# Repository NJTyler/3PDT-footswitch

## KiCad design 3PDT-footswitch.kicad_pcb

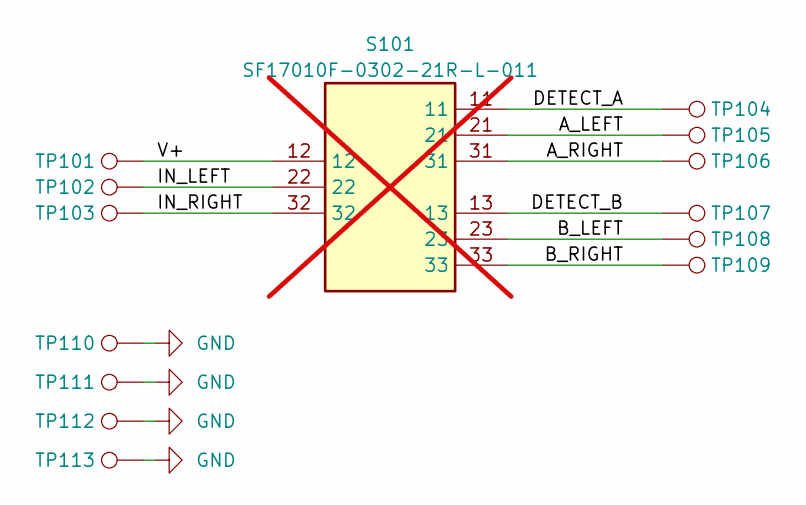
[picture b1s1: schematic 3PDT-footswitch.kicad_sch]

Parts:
S101: SF17010F-0302-21R-L-011; SF17010F030221RL011; Manufacturer_Part_Number SF17010F-0302-21R-L-011; Mouser Part Number 107-SF17010F-32-21RL; not fitted
TP101, TP102, TP103, TP104, TP105, TP106, TP107, TP108, TP109, TP110, TP111, TP112, TP113: TestPoint; TestPoint_Pad_D2.0mm

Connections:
/A_LEFT: S101.21, TP105.1
/A_RIGHT: S101.31, TP106.1
/B_LEFT: S101.23, TP108.1
/B_RIGHT: S101.33, TP109.1
/DETECT_A: S101.11, TP104.1
/DETECT_B: S101.13, TP107.1
/IN_LEFT: S101.22, TP102.1
/IN_RIGHT: S101.32, TP103.1
/V+: S101.12, TP101.1
GND: TP110.1, TP111.1, TP112.1, TP113.1

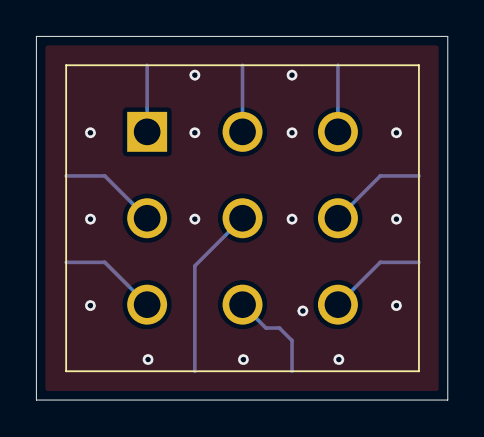
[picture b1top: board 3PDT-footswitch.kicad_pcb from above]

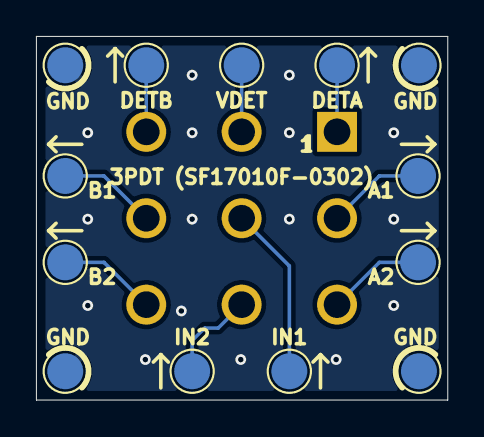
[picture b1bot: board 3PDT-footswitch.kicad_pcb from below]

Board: 2 copper layers, 22.9 x 20.2 mm, 14 parts (13 on the bottom side), 10 nets.

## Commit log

2025-01-29 improved simple routing
2025-01-29 smaller pcb, added silkscreens
2025-01-29 added footswitch id to silkscreen
2025-01-30 added panelised pcb for manufacture
